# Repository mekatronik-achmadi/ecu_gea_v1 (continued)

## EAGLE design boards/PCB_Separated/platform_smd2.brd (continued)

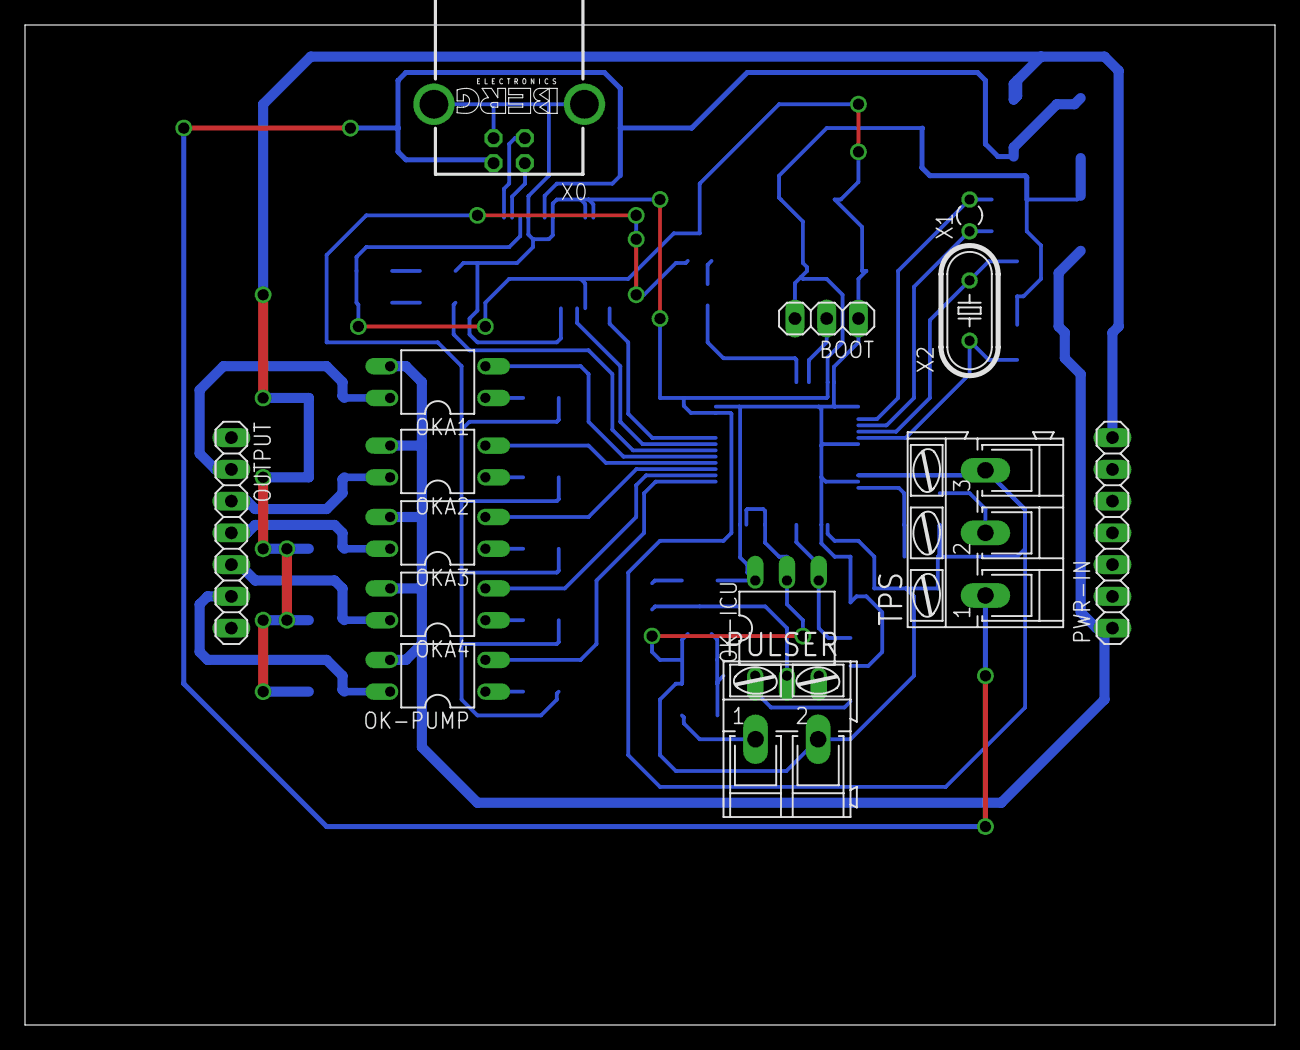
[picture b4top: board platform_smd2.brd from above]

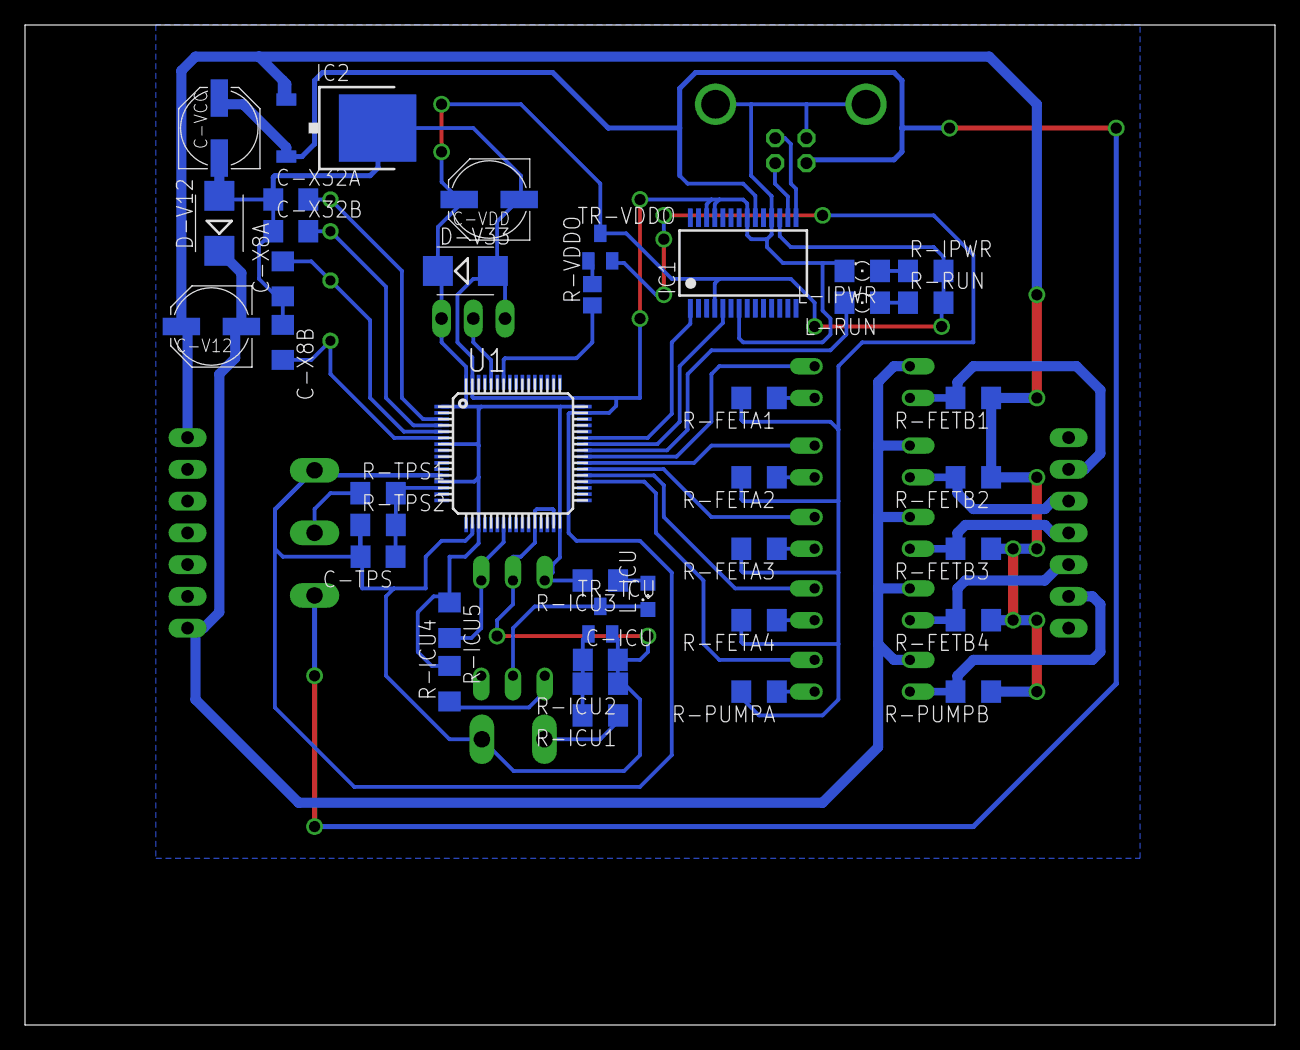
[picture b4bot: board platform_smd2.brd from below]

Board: 2 copper layers, 100.0 x 80.0 mm, 53 parts (39 on the bottom side), 43 nets.

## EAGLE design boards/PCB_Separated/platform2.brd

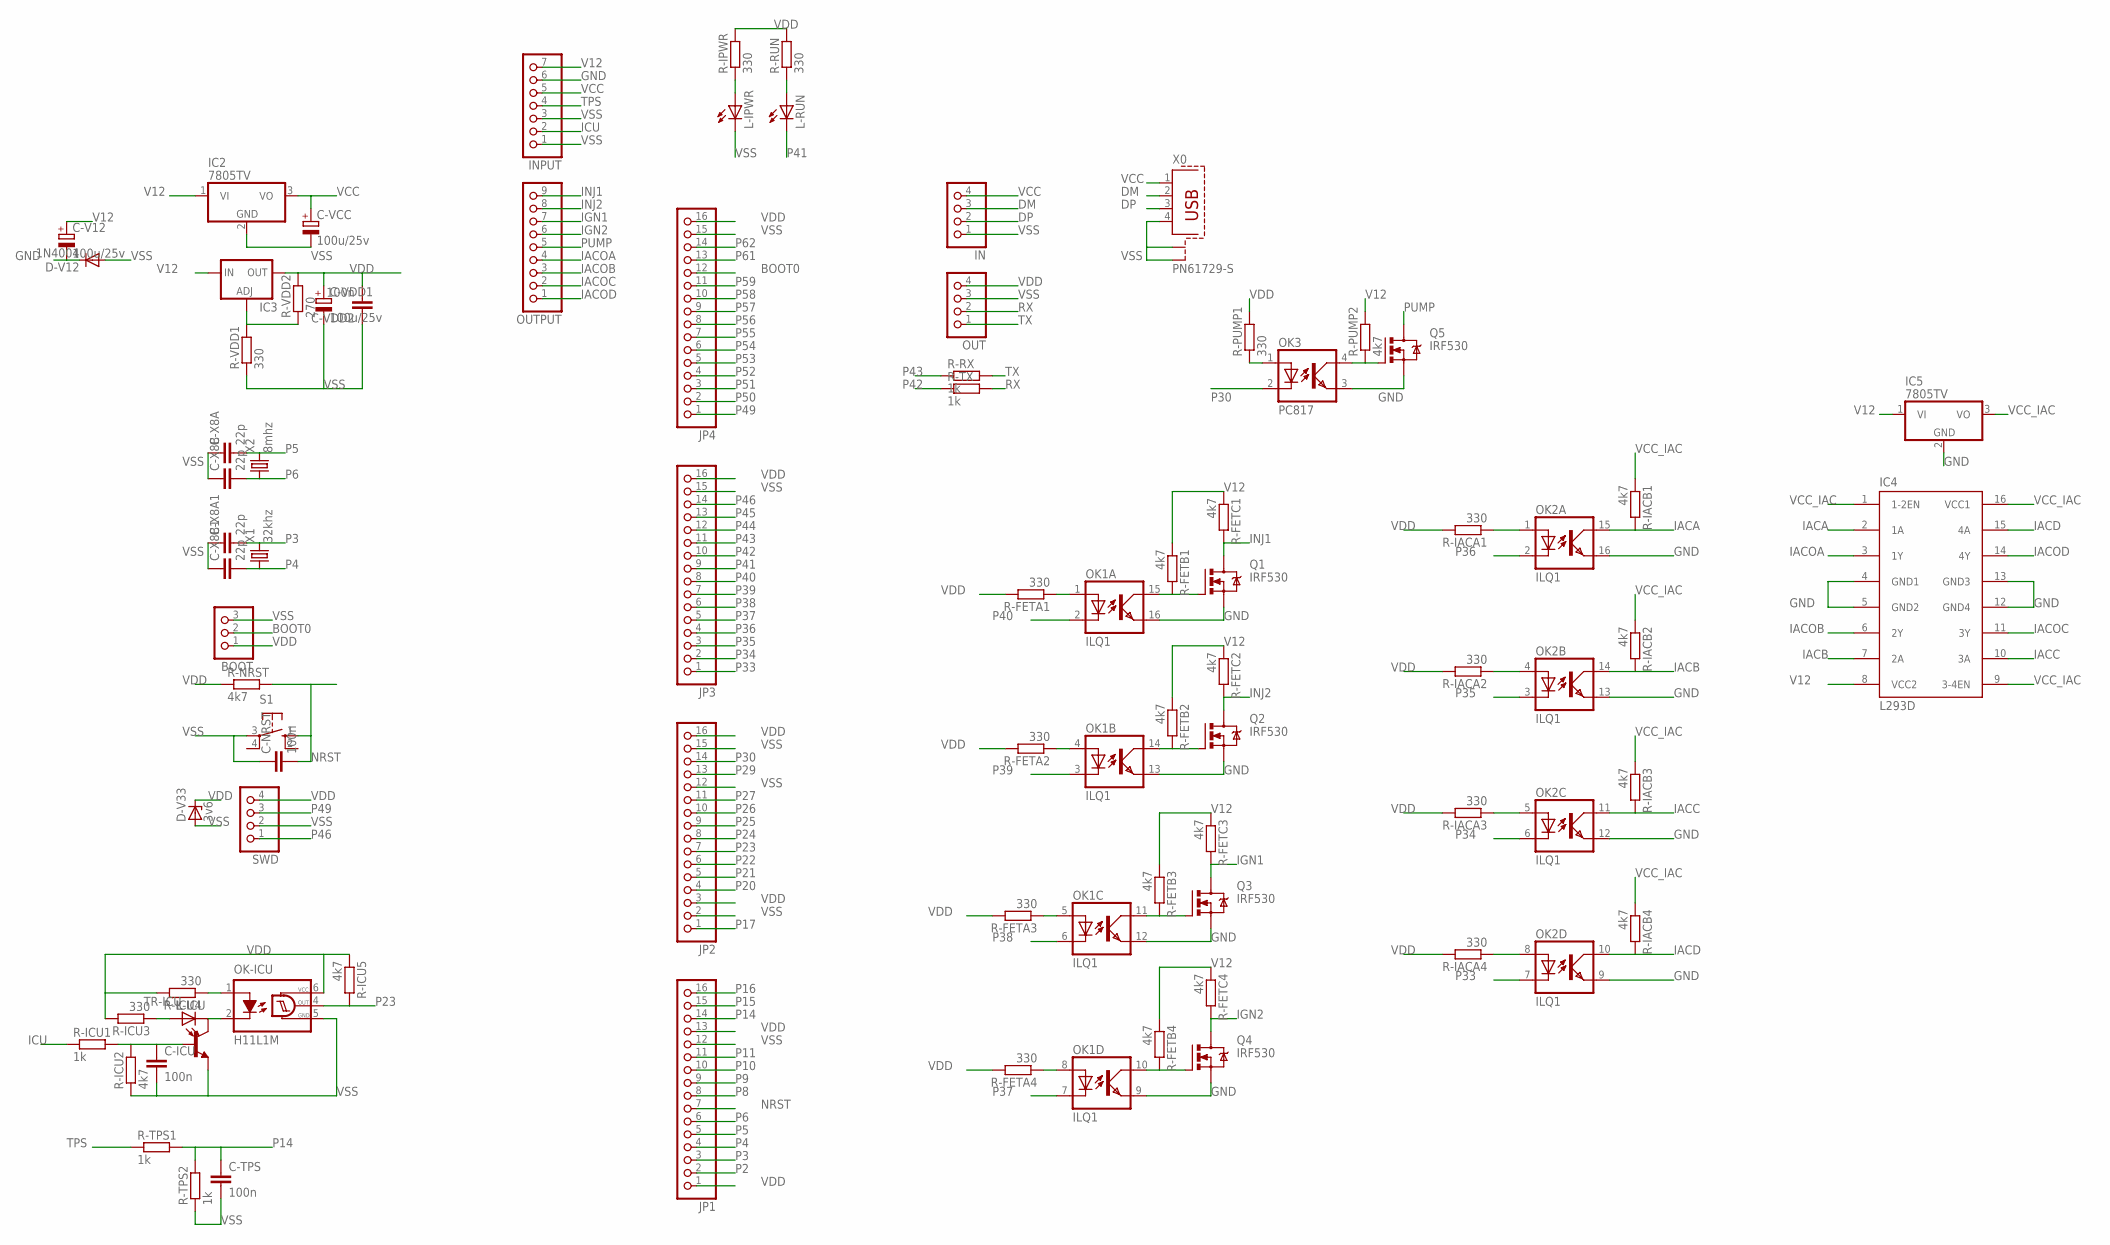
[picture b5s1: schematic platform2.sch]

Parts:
BOOT: PINHD-1X3; 1X03
C-ICU: 100n; C050-024X044
C-NRST: 100n; C050-024X044
C-TPS: 100n; C050-024X044
C-V12: 100u/25v; E2-5
C-VCC: 100u/25v; E2-5
C-VDD1: 100u/25v; E2-5
C-VDD2: 100n; C050-024X044
C-X8A, C-X8A1, C-X8B, C-X8B1: 22p; C025-024X044
D-V12: 1N4004; DO41-10
D-V33: 3v6; ZDIO-7.5
IC2, IC5: 7805TV; TO220V
IC3: LM317TS; 317TS
IC4: L293D; DIL16
IN: PINHD-1X4; 1X04
INPUT: PINHD-1X7; 1X07
JP1, JP2, JP3, JP4: PINHD-1X16; 1X16
L-ICU: LED3MM
L-IPWR: LED3MM
L-RUN: LED3MM
OK1, OK2: ILQ1; DIL16
OK3: PC817; DIL04
OK-ICU: H11L1M; DIL06
OUT: PINHD-1X4; 1X04
OUTPUT: PINHD-1X9; 1X09
Q1, Q2, Q3, Q4, Q5: IRF530; TO220BV
R-FETA1, R-FETA2, R-FETA3, R-FETA4: 330; 0204/7
R-FETB1, R-FETB2, R-FETB3, R-FETB4: 4k7; 0204/7
R-FETC1, R-FETC2, R-FETC3, R-FETC4: 4k7; 0204/7
R-IACA1, R-IACA2, R-IACA3, R-IACA4: 330; 0204/7
R-IACB1, R-IACB2, R-IACB3, R-IACB4: 4k7; 0204/7
R-ICU1: 1k; 0204/7
R-ICU2, R-ICU5: 4k7; 0204/7
R-ICU3, R-ICU4: 330; 0204/7
R-IPWR: 330; 0204/7
R-NRST: 4k7; 0204/7
R-PUMP1: 330; 0204/7
R-PUMP2: 4k7; 0204/7
R-RUN: 330; 0204/7
R-RX: 1k; 0204/7
R-TPS1, R-TPS2: 1k; 0204/7
R-TX: 1k; 0204/7
R-VDD1: 330; 0204/7
R-VDD2: 270; 0204/7
S1: 10-XX; B3F-10XX
SWD: PINHD-1X4; 1X04
TR-ICU: 2N3904-NPN-TO92-EBC; TO92-EBC
X0: PN61729-S
X1: 32khz; TC26V
X2: 8mhz; HC49U-V

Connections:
BOOT0: BOOT.2, JP4.12
DM: IN.3, X0.2
DP: IN.2, X0.3
GND: C-V12.-, D-V12.C, IC4.4 (GND1), IC4.5 (GND2), IC4.12 (GND4), IC4.13 (GND3), IC5.2 (GND), INPUT.6, OK1.9 (EMIT), OK1.12 (EMIT), OK1.13 (EMIT), OK1.16 (EMIT), OK2.9 (EMIT), OK2.12 (EMIT), OK2.13 (EMIT), OK2.16 (EMIT), OK3.3 (EMIT), Q1.S, Q2.S, Q3.S, Q4.S, Q5.S
IACA: IC4.2 (1A), OK2.15 (COL), R-IACB1.2
IACB: IC4.7 (2A), OK2.14 (COL), R-IACB2.2
IACC: IC4.10 (3A), OK2.11 (COL), R-IACB3.2
IACD: IC4.15 (4A), OK2.10 (COL), R-IACB4.2
IACOA: IC4.3 (1Y), OUTPUT.4
IACOB: IC4.6 (2Y), OUTPUT.3
IACOC: IC4.11 (3Y), OUTPUT.2
IACOD: IC4.14 (4Y), OUTPUT.1
ICU: INPUT.2, R-ICU1.1
IGN1: OUTPUT.7, Q3.D, R-FETC3.2
IGN2: OUTPUT.6, Q4.D, R-FETC4.2
INJ1: OUTPUT.9, Q1.D, R-FETC1.2
INJ2: OUTPUT.8, Q2.D, R-FETC2.2
unnamed: OK1.14 (COL), Q2.G, R-FETB2.2
unnamed: C-ICU.1, R-ICU1.2, R-ICU2.2, TR-ICU.B
unnamed: L-ICU.K (C), OK-ICU.2 (C), TR-ICU.C
unnamed: OK-ICU.1 (A), R-ICU4.1
unnamed: L-ICU.A, R-ICU3.1
unnamed: L-IPWR.A, R-IPWR.1
unnamed: L-RUN.A, R-RUN.1
unnamed: OK3.1 (A), R-PUMP1.1
unnamed: OK2.1 (A), R-IACA1.1
unnamed: OK1.15 (COL), Q1.G, R-FETB1.2
unnamed: OK1.4 (A), R-FETA2.1
unnamed: OK1.1 (A), R-FETA1.1
unnamed: OK1.11 (COL), Q3.G, R-FETB3.2
unnamed: OK1.5 (A), R-FETA3.1
unnamed: OK1.10 (COL), Q4.G, R-FETB4.2
unnamed: OK1.8 (A), R-FETA4.1
unnamed: OK2.4 (A), R-IACA2.1
unnamed: OK3.4 (COL), Q5.G, R-PUMP2.1
unnamed: OK2.5 (A), R-IACA3.1
unnamed: OK2.8 (A), R-IACA4.1
unnamed: IC3.1 (ADJ), R-VDD1.2, R-VDD2.1
NRST: C-NRST.2, JP1.7, R-NRST.2, S1.1 (S)
P2: JP1.2
P3: C-X8A1.2, JP1.3, X1.2
P4: C-X8B1.2, JP1.4, X1.1
P5: C-X8A.2, JP1.5, X2.2
P6: C-X8B.2, JP1.6, X2.1
P8: JP1.8
P9: JP1.9
P10: JP1.10
P11: JP1.11
P14: C-TPS.1, JP1.14, R-TPS1.2, R-TPS2.2
P15: JP1.15
P16: JP1.16
P17: JP2.1
P20: JP2.4
P21: JP2.5
P22: JP2.6
P23: JP2.7, OK-ICU.4 (OUT), R-ICU5.2
P24: JP2.8
P25: JP2.9
P26: JP2.10
P27: JP2.11
P29: JP2.13
P30: JP2.14, OK3.2 (C)
P33: JP3.1, OK2.7 (C)
P34: JP3.2, OK2.6 (C)
P35: JP3.3, OK2.3 (C)
P36: JP3.4, OK2.2 (C)
P37: JP3.5, OK1.7 (C)
P38: JP3.6, OK1.6 (C)
P39: JP3.7, OK1.3 (C)
P40: JP3.8, OK1.2 (C)
P41: JP3.9, L-RUN.K (C)
P42: JP3.10, R-TX.1
P43: JP3.11, R-RX.1
P44: JP3.12
P45: JP3.13
P46: JP3.14, SWD.1
P49: JP4.1, SWD.3
P50: JP4.2
P51: JP4.3
P52: JP4.4
P53: JP4.5
P54: JP4.6
P55: JP4.7
P56: JP4.8
P57: JP4.9
P58: JP4.10
P59: JP4.11
P61: JP4.13
P62: JP4.14
PUMP: OUTPUT.5, Q5.D
RX: OUT.2, R-TX.2
TPS: INPUT.4, R-TPS1.1
TX: OUT.1, R-RX.2
V12: C-V12.+, IC2.1 (VI), IC3.3 (IN), IC4.8 (VCC2), IC5.1 (VI), INPUT.7, R-FETB1.1, R-FETB2.1, R-FETB3.1, R-FETB4.1, R-FETC1.1, R-FETC2.1, R-FETC3.1, R-FETC4.1, R-PUMP2.2
VCC: C-VCC.+, IC2.3 (VO), IN.4, INPUT.5, X0.1
VCC_IAC: IC4.1 (1-2EN), IC4.9 (3-4EN), IC4.16 (VCC1), IC5.3 (VO), R-IACB1.1, R-IACB2.1, R-IACB3.1, R-IACB4.1
VDD: BOOT.1, C-VDD1.+, C-VDD2.2, D-V33.C, IC3.2 (OUT), JP1.1, JP1.13, JP2.3, JP2.16, JP3.16, JP4.16, OK-ICU.6 (VCC), OUT.4, R-FETA1.2, R-FETA2.2, R-FETA3.2, R-FETA4.2, R-IACA1.2, R-IACA2.2, R-IACA3.2, R-IACA4.2, R-ICU3.2, R-ICU4.2, R-ICU5.1, R-IPWR.2, R-NRST.1, R-PUMP1.2, R-RUN.2, R-VDD2.2, SWD.4
VSS: BOOT.3, C-ICU.2, C-NRST.1, C-TPS.2, C-VCC.-, C-VDD1.-, C-VDD2.1, C-X8A.1, C-X8A1.1, C-X8B.1, C-X8B1.1, D-V12.A, D-V33.A, IC2.2 (GND), IN.1, INPUT.1, INPUT.3, JP1.12, JP2.2, JP2.12, JP2.15, JP3.15, JP4.15, L-IPWR.K (C), OK-ICU.5 (GND), OUT.3, R-ICU2.1, R-TPS2.1, R-VDD1.1, S1.3, SWD.2, TR-ICU.E, X0.4, X0.S1, X0.S2

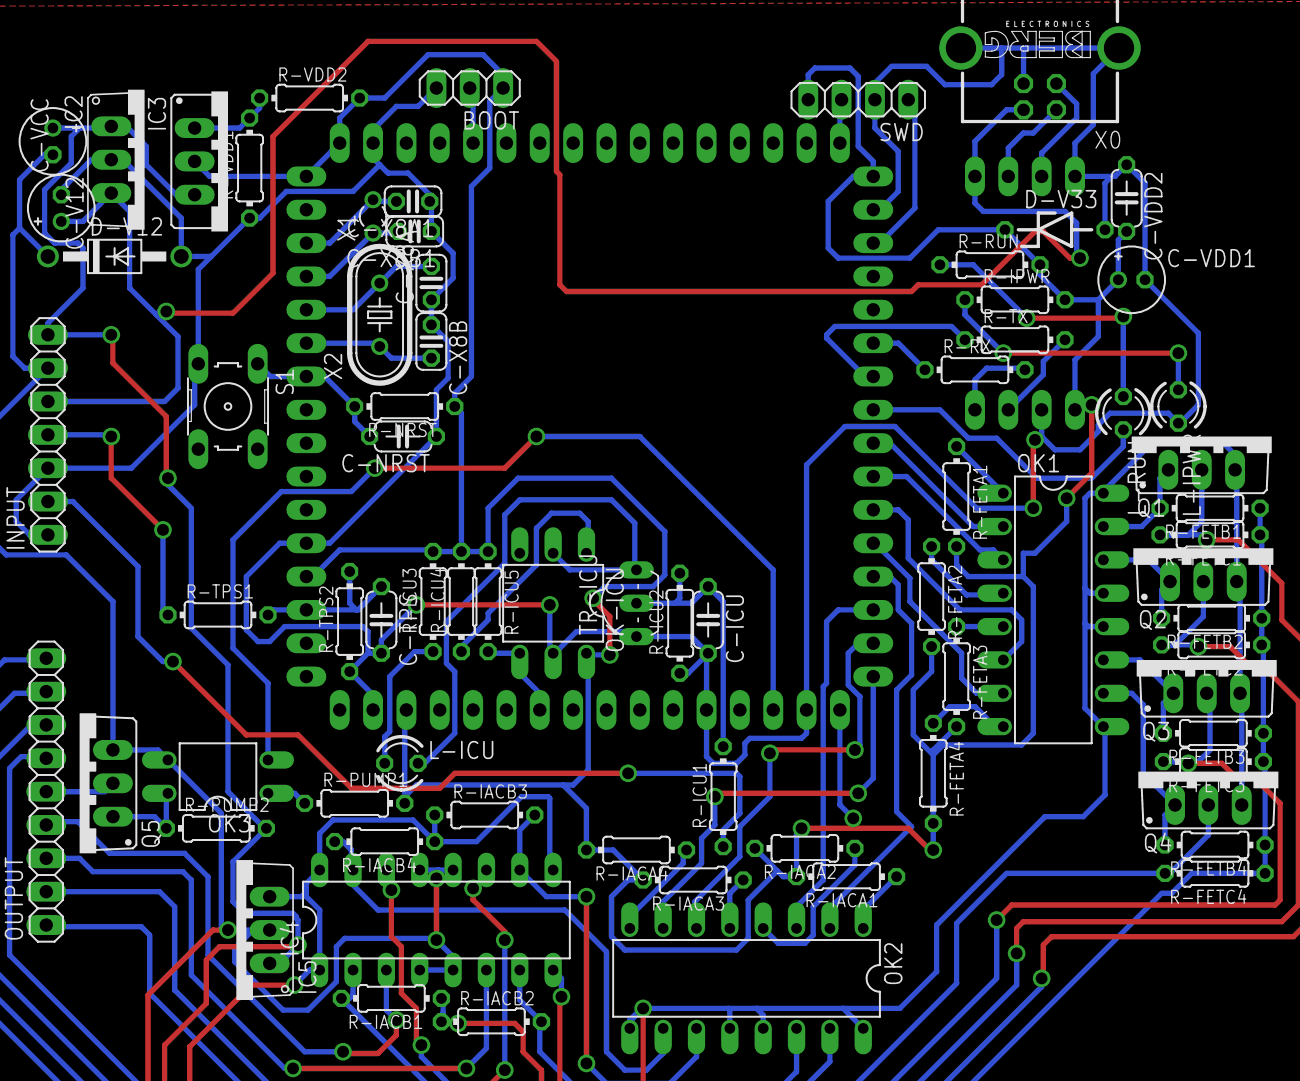
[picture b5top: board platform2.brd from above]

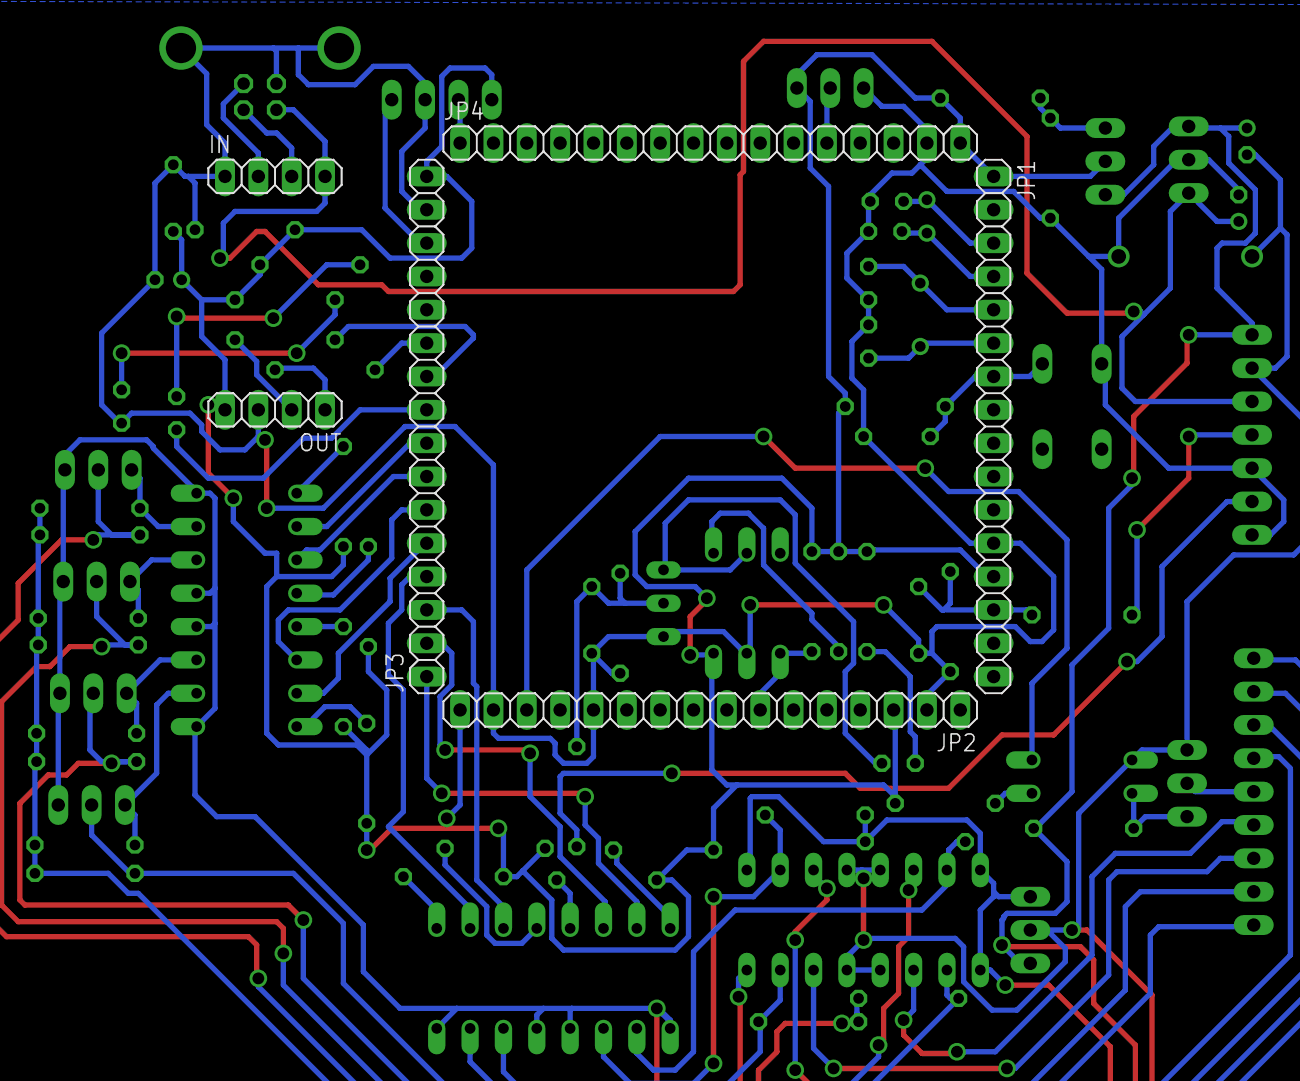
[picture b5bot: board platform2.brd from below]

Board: 2 copper layers, 80 parts (6 on the bottom side), 68 nets.

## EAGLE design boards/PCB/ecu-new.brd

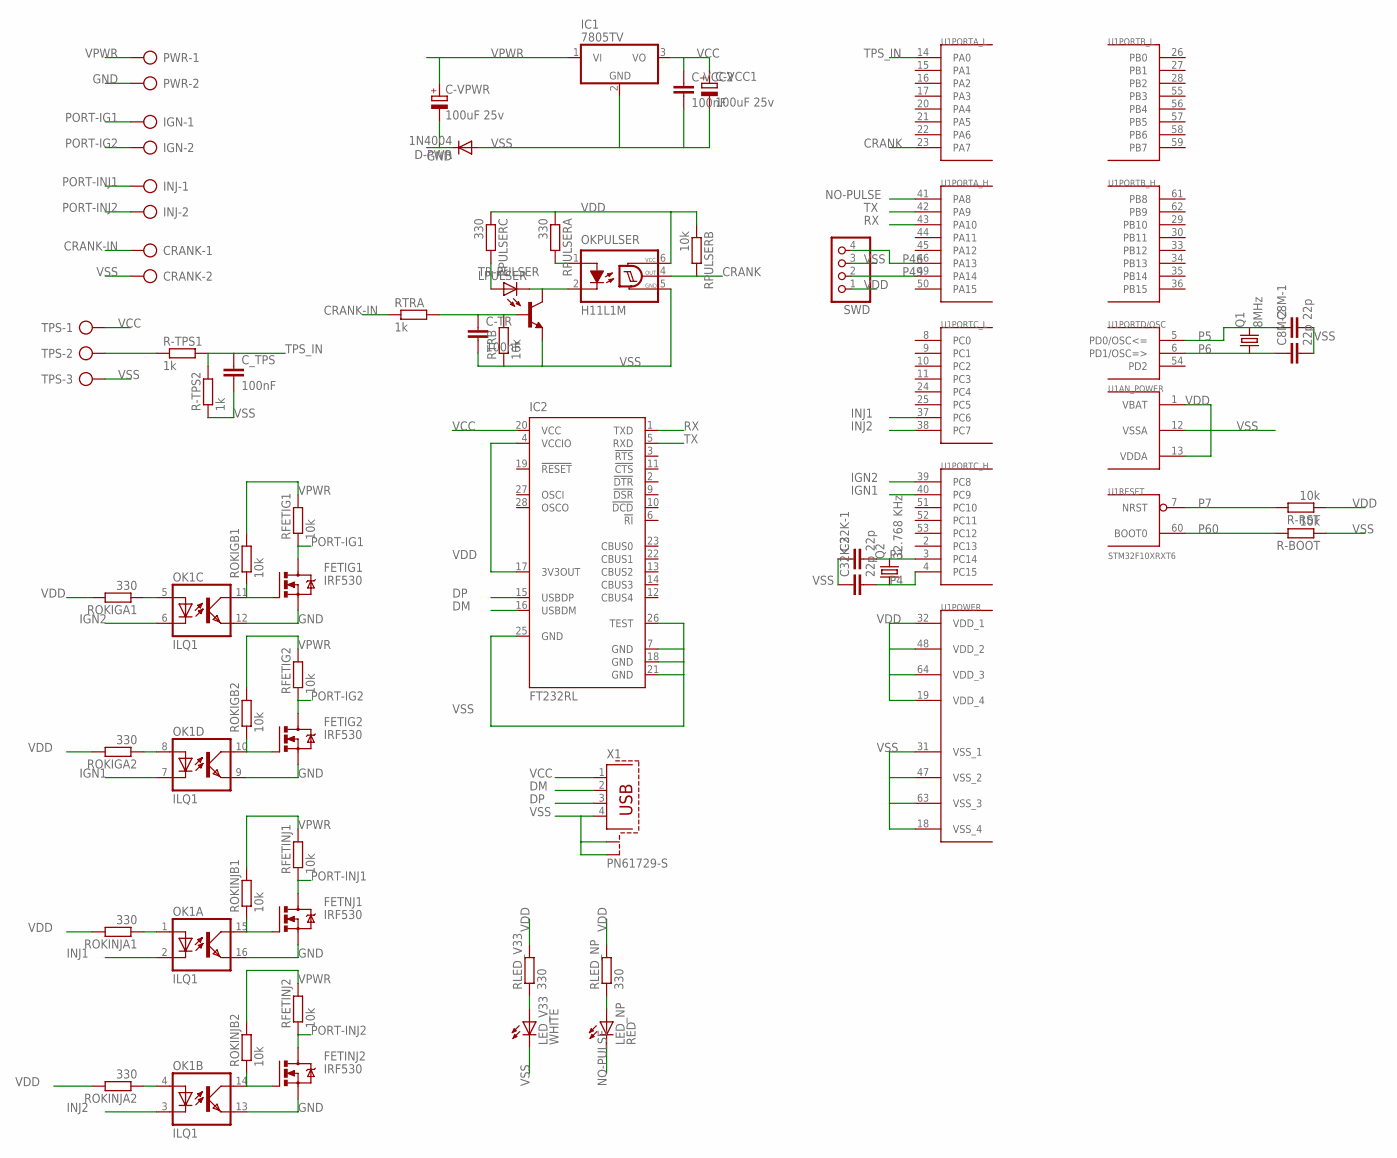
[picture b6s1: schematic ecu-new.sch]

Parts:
C8M-1, C8M-2, C32K-1, C32K-2: 22p; C025-030X050
C-TR: 100nF; C050-024X044
C-VCC1: 100uF 25v; E2,5-7
C-VCC2: 100nF; C050-024X044
C-VPWR: 100uF 25v; E2,5-7
CRANK: AK300/2
C_TPS: 100nF; C050-024X044
D-PWR: 1N4004; DO41-10
FETIG1, FETIG2: IRF530; TO220BV
FETINJ2: IRF530; TO220BV
FETNJ1: IRF530; TO220BV
IC1: 7805TV; TO220V
IC2: FT232RL; SSOP28
IGN: AK300/2
INJ: AK300/2
LED_NP: RED; LED3MM
LED_V33: WHITE; LED3MM
LPULSER: LED3MM
OK1: ILQ1; DIL16
OKPULSER: H11L1M; DIL06
PWR: AK300/2
Q1: 8MHz; HC49/S
Q2: 32.768 KHz; TC26H
R-BOOT: 10k; 0204/7
R-RST: 10k; 0204/7
R-TPS1, R-TPS2: 1k; 0204/7
RFETIG1, RFETIG2: 10k; 0204/7
RFETINJ1, RFETINJ2: 10k; 0204/7
RLED_NP: 330; 0204/7
RLED_V33: 330; 0204/7
ROKIGA1, ROKIGA2: 330; 0204/7
ROKIGB1, ROKIGB2: 10k; 0204/7
ROKINJA1, ROKINJA2: 330; 0204/7
ROKINJB1, ROKINJB2: 10k; 0204/7
RPULSERA: 330; 0204/7
RPULSERB: 10k; 0204/7
RPULSERC: 330; 0204/7
RTRA: 1k; 0204/7
RTRB: 10k; 0204/7
SWD: PINHD-1X4; 1X04
TPS: AK300/3
TR-PULSER: 2N3904-NPN-TO92-EBC; TO92-EBC
U1: STM32F10XRXT6; TQFP64
X1: PN61729-S

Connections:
CRANK: OKPULSER.4 (OUT), RPULSERB.2, U1.23 (PA7)
CRANK-IN: CRANK.1, RTRA.1
DM: IC2.16 (USBDM), X1.2
DP: IC2.15 (USBDP), X1.3
GND: C-VPWR.-, D-PWR.C, FETIG1.S, FETIG2.S, FETINJ2.S, FETNJ1.S, OK1.9 (EMIT), OK1.12 (EMIT), OK1.13 (EMIT), OK1.16 (EMIT), PWR.2
IGN1: OK1.7 (C), U1.40 (PC9)
IGN2: OK1.6 (C), U1.39 (PC8)
INJ1: OK1.2 (C), U1.37 (PC6)
INJ2: OK1.3 (C), U1.38 (PC7)
unnamed: OK1.4 (A), ROKINJA2.1
unnamed: C-TR.1, RTRA.2, RTRB.2, TR-PULSER.B
unnamed: OKPULSER.1 (A), RPULSERA.2
unnamed: LPULSER.A, RPULSERC.2
unnamed: LPULSER.K (C), OKPULSER.2 (C), TR-PULSER.C
unnamed: OK1.5 (A), ROKIGA1.1
unnamed: OK1.8 (A), ROKIGA2.1
unnamed: OK1.1 (A), ROKINJA1.1
unnamed: FETIG2.G, OK1.10 (COL), ROKIGB2.1
unnamed: FETNJ1.G, OK1.15 (COL), ROKINJB1.1
unnamed: FETIG1.G, OK1.11 (COL), ROKIGB1.1
unnamed: FETINJ2.G, OK1.14 (COL), ROKINJB2.1
unnamed: R-TPS1.1, TPS.2
unnamed: LED_V33.A, RLED_V33.1
unnamed: LED_NP.A, RLED_NP.1
NO-PULSE: LED_NP.K (C), U1.41 (PA8)
P3: C32K-1.2, Q2.2, U1.3 (PC14)
P4: C32K-2.2, Q2.1, U1.4 (PC15)
P5: C8M-1.1, Q1.2, U1.5 (PD0/OSC<=)
P6: C8M-2.1, Q1.1, U1.6 (PD1/OSC=>)
P7: R-RST.2, U1.7 (NRST)
P46: SWD.4, U1.46 (PA13)
P49: SWD.2, U1.49 (PA14)
P60: R-BOOT.2, U1.60 (BOOT0)
PORT-IG1: FETIG1.D, IGN.1, RFETIG1.1
PORT-IG2: FETIG2.D, IGN.2, RFETIG2.1
PORT-INJ1: FETNJ1.D, INJ.1, RFETINJ1.1
PORT-INJ2: FETINJ2.D, INJ.2, RFETINJ2.1
RX: IC2.1 (TXD), U1.43 (PA10)
TPS_IN: C_TPS.1, R-TPS1.2, R-TPS2.2, U1.14 (PA0)
TX: IC2.5 (RXD), U1.42 (PA9)
VCC: C-VCC1.+, C-VCC2.1, IC1.3 (VO), IC2.20 (VCC), TPS.1, X1.1
VDD: IC2.4 (VCCIO), IC2.17 (3V3OUT), OKPULSER.6 (VCC), R-RST.1, RLED_NP.2, RLED_V33.2, ROKIGA1.2, ROKIGA2.2, ROKINJA1.2, ROKINJA2.2, RPULSERA.1, RPULSERB.1, RPULSERC.1, SWD.1, U1.1 (VBAT), U1.13 (VDDA), U1.19 (VDD_4), U1.32 (VDD_1), U1.48 (VDD_2), U1.64 (VDD_3)
VPWR: C-VPWR.+, IC1.1 (VI), PWR.1, RFETIG1.2, RFETIG2.2, RFETINJ1.2, RFETINJ2.2, ROKIGB1.2, ROKIGB2.2, ROKINJB1.2, ROKINJB2.2
VSS: C8M-1.2, C8M-2.2, C32K-1.1, C32K-2.1, C-TR.2, C-VCC1.-, C-VCC2.2, CRANK.2, C_TPS.2, D-PWR.A, IC1.2 (GND), IC2.7 (GND), IC2.18 (GND), IC2.21 (GND), IC2.25 (GND), IC2.26 (TEST), LED_V33.K (C), OKPULSER.5 (GND), R-BOOT.1, R-TPS2.1, RTRB.1, SWD.3, TPS.3, TR-PULSER.E, U1.12 (VSSA), U1.18 (VSS_4), U1.31 (VSS_1), U1.47 (VSS_2), U1.63 (VSS_3), X1.4, X1.S1, X1.S2

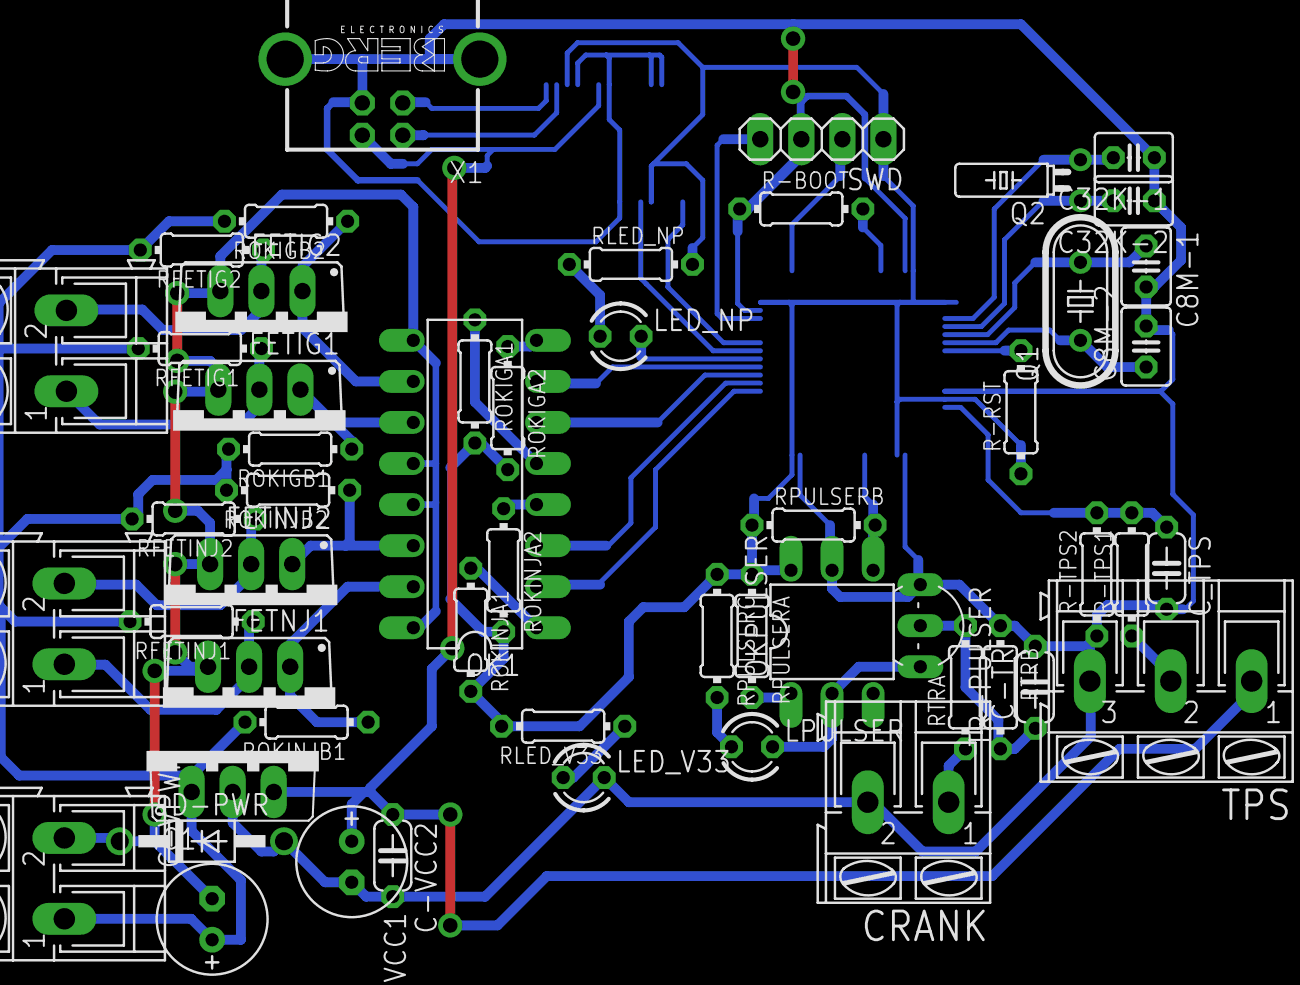
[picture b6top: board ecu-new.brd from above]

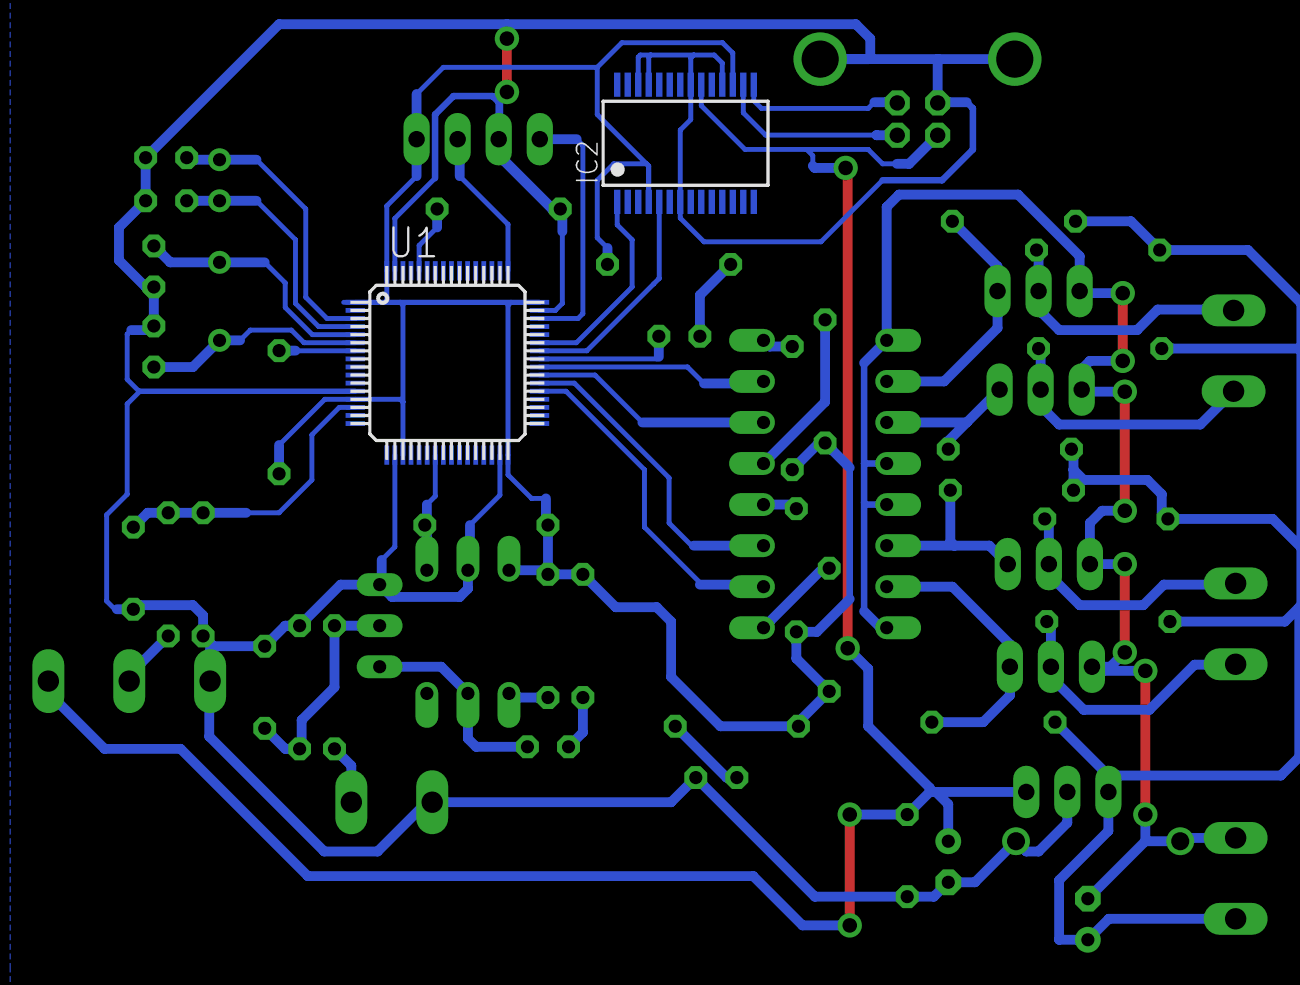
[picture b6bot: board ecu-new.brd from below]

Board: 2 copper layers, 55 parts (2 on the bottom side), 44 nets.

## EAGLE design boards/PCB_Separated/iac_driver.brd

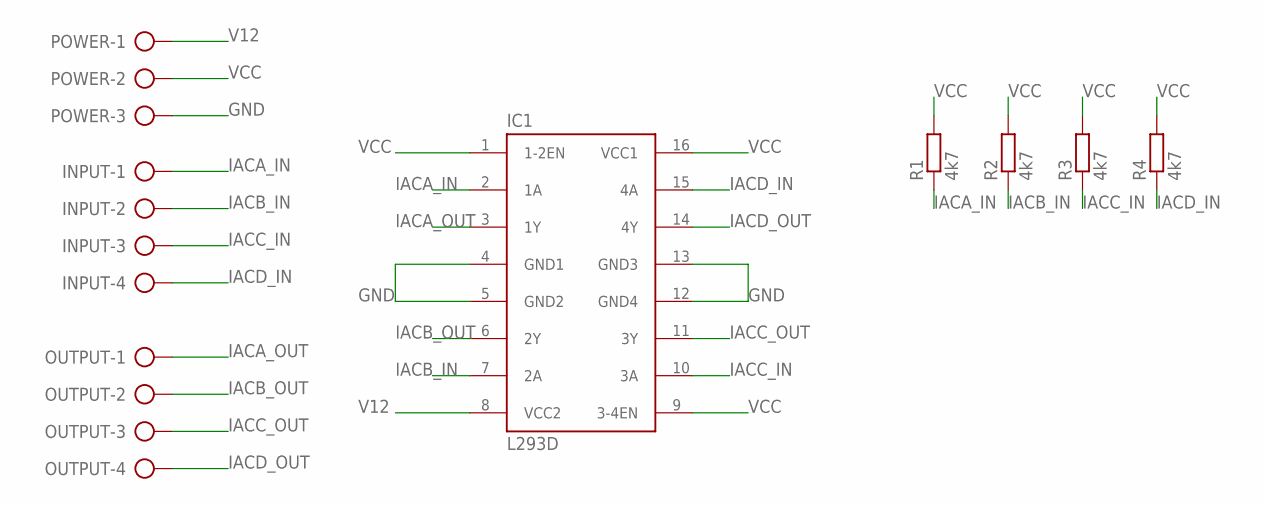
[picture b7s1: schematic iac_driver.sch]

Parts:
IC1: L293D; DIL16
INPUT: AK500/4
OUTPUT: AK500/4
POWER: AK500/3
R1, R2, R3, R4: 4k7; 0204/7

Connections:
GND: IC1.4 (GND1), IC1.5 (GND2), IC1.12 (GND4), IC1.13 (GND3), POWER.3
IACA_IN: IC1.2 (1A), INPUT.1, R1.1
IACA_OUT: IC1.3 (1Y), OUTPUT.1
IACB_IN: IC1.7 (2A), INPUT.2, R2.1
IACB_OUT: IC1.6 (2Y), OUTPUT.2
IACC_IN: IC1.10 (3A), INPUT.3, R3.1
IACC_OUT: IC1.11 (3Y), OUTPUT.3
IACD_IN: IC1.15 (4A), INPUT.4, R4.1
IACD_OUT: IC1.14 (4Y), OUTPUT.4
V12: IC1.8 (VCC2), POWER.1
VCC: IC1.1 (1-2EN), IC1.9 (3-4EN), IC1.16 (VCC1), POWER.2, R1.2, R2.2, R3.2, R4.2

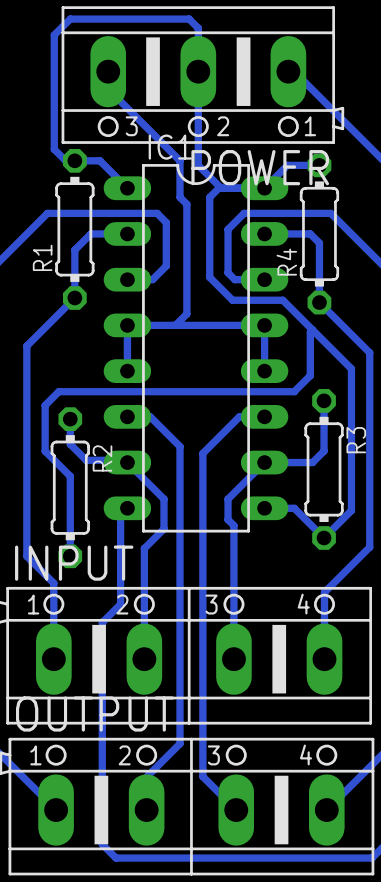
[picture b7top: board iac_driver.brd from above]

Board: 2 copper layers, 8 parts (0 on the bottom side), 11 nets.

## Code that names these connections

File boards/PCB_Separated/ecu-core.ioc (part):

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Mcu.Name=STM32F103R(8-B)Tx
Mcu.Package=LQFP64
PA0-WKUP.Mode=IN0
PA0-WKUP.Signal=ADC1_IN0
PA1.Mode=IN1
PA1.Signal=ADC1_IN1
PA10.Mode=Asynchronous
PA10.Signal=USART1_RX
PA13.Mode=Serial-Wire
PA13.Signal=SYS_JTMS-SWDIO
PA14.Mode=Serial-Wire
PA14.Signal=SYS_JTCK-SWCLK
PA2.Mode=IN2
PA2.Signal=ADC1_IN2
PA3.Mode=IN3
PA3.Signal=ADC1_IN3
PA7.Mode=PWM-Input-2
PA7.Signal=TIM3_CH2
PA8.Signal=GPIO_Output
PA9.Mode=Asynchronous
PA9.Signal=USART1_TX
PB12.Signal=GPIO_Output
PB13.Signal=GPIO_Output
PB14.Signal=GPIO_Output
PB15.Signal=GPIO_Output
PB6.Signal=GPIO_Output
PB7.Signal=GPIO_Output
PC14-OSC32_IN.Mode=LSE-External-Oscillator
PC14-OSC32_IN.Signal=SYS_OSC32_IN
PC15-OSC32_OUT.Mode=LSE-External-Oscillator
PC15-OSC32_OUT.Signal=SYS_OSC32_OUT
PC6.Signal=GPIO_Output
PC7.Signal=GPIO_Output
PC8.Signal=GPIO_Output
PC9.Signal=GPIO_Output
PD0-OSC_IN.Mode=HSE-External-Oscillator
PD0-OSC_IN.Signal=SYS_OSC_IN
PD1-OSC_OUT.Mode=HSE-External-Oscillator
PD1-OSC_OUT.Signal=SYS_OSC_OUT

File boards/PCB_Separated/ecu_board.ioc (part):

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Mcu.Name=STM32F103R(8-B)Tx
Mcu.Package=LQFP64
PA0-WKUP.Mode=IN0
PA0-WKUP.Signal=ADC1_IN0
PA1.Mode=IN1
PA1.Signal=ADC1_IN1
PA10.Mode=Asynchronous
PA10.Signal=USART1_RX
PA2.Mode=IN2
PA2.Signal=ADC1_IN2
PA3.Mode=IN3
PA3.Signal=ADC1_IN3
PA4.Mode=IN4
PA4.Signal=ADC1_IN4
PA5.Mode=IN5
PA5.Signal=ADC1_IN5
PA7.Mode=PWM-Input-2
PA7.Signal=TIM3_CH2
PA9.Mode=Asynchronous
PA9.Signal=USART1_TX
PB12.Signal=GPIO_Output
PB13.Signal=GPIO_Output
PB14.Signal=GPIO_Output
PB15.Signal=GPIO_Output
PB2.Signal=GPIO_Input
PC14-OSC32_IN.Mode=LSE-External-Oscillator
PC14-OSC32_IN.Signal=SYS_OSC32_IN
PC15-OSC32_OUT.Mode=LSE-External-Oscillator
PC15-OSC32_OUT.Signal=SYS_OSC32_OUT
PC6.Signal=GPIO_Output
PC7.Signal=GPIO_Output
PC8.Signal=GPIO_Output
PC9.Signal=GPIO_Output
PD0-OSC_IN.Mode=HSE-External-Oscillator
PD0-OSC_IN.Signal=SYS_OSC_IN
PD1-OSC_OUT.Mode=HSE-External-Oscillator
PD1-OSC_OUT.Signal=SYS_OSC_OUT

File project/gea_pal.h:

#ifndef GEA2_PAL
#define GEA2_PAL

#define led 8

#define inj_1 9
#define inj_2 8
#define ign_1 7
#define ign_2 6
#define pump 15

//sistem tanpa pullup
//#define output 6
//sistem dengan pullup
#define output 14

#define no_pulse palTogglePad(GPIOA,led)

#define on_inj1 palSetPad(GPIOC,inj_1)
#define off_inj1 palClearPad(GPIOC,inj_1)

#define on_inj2 palSetPad(GPIOC,inj_2)
#define off_inj2 palClearPad(GPIOC,inj_2)

#define off_ign1 palSetPad(GPIOC,ign_1)
#define on_ign1 palClearPad(GPIOC,ign_1)

#define off_ign2 palSetPad(GPIOC,ign_2)
#define on_ign2 palClearPad(GPIOC,ign_2)

#define on_pump palSetPad(GPIOB,pump)
#define off_pump palClearPad(GPIOB,pump)

//sistem tanpa pullup
//#define out_active palSetPad(GPIOB,output)
//sistem dengan pullup
#define out_active palSetPad(GPIOB,output)

#define interval chThdSleepMilliseconds(6);

#define IACA 15
#define IACB 14
#define IACC 13
#define IACD 12

#define IACA_H palSetPad(GPIOB,IACA)
#define IACA_L palClearPad(GPIOB,IACA)

#define IACB_H palSetPad(GPIOB,IACB)
#define IACB_L palClearPad(GPIOB,IACB)

#define IACC_H palSetPad(GPIOB,IACC)
#define IACC_L palClearPad(GPIOB,IACC)

#define IACD_H palSetPad(GPIOB,IACD)
#define IACD_L palClearPad(GPIOB,IACD)

void Pal_Setup(void);
void Iac_CW(uint8_t loop);
void Iac_CCW(uint8_t loop);
void Iac_Start(void);

#endif  

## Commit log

2014-03-09 add a new separatedly-style board
2014-03-10 Change License to GPL v3
2014-03-10 Modify Board. Core and FTDI become one file
2014-03-11 add platform board
2014-03-15 Proceed to use GPT
2014-03-15 added GPT functions
2014-03-15 1st GPT use trial
2014-03-15 edit serial interface data
2014-03-16 perbaikan konversi sudut ke tick timer
2014-03-18 Improve engine settings and add shell data_and_test routine
2014-03-18 improved test and data function
2014-03-19 re-add info function to shell
2014-03-20 add some toggle action to output
2014-03-22 copy from james's PC
2014-03-26 -delete a useless sch pics -add ecu io pins diagram -add a GND to VSS line on FTDI. Hopefully internally connected with other GND pins -progress new separated ecu board.
2014-03-26 progress to build new ecu boards
2014-03-26 progress add function to IAC
2014-04-04 add connector board
2014-04-04 add label on connector design
2014-04-08 re-config output to Injector and Ignitor
2014-04-09 progress buat IAC
2014-04-10 progress for IAC
    move resistor on mainborad to IAC driver to get 5v logic instead of 12v logic
2014-04-13 IAC progress. Valve already driven, but there a problem with voltage while USB connected to PC
2014-04-13 add more cycle for opening iac (CCW rotation)
    L293D circuit should use separate VCC regulator
2014-04-13 IAC over opened
2014-04-13 IAC still bad performance
2014-04-16 new commit and IAC progress
2014-04-17 IAC seem good
2014-04-22 add Qt-based Engine Interface and Qt-based Engine Calculator
2014-04-23 interface progress
2014-04-26 progress interface
2014-05-02 eeprom emulation
2014-05-03 -memory and interfacing on embedded core seems good by increase max argument on shell -GUI on Qt still on progress
2014-05-04 Interface rancangan oke
2014-05-04 - move injection trigger to TDC
    -next:
    1. injection duration to 2D Array (RPM and TPS)
    2. injection off to RPM settings
2014-05-04 still bad
2014-05-11 problem with tick for 1 degree
2014-05-12 progress semakin pusing
2014-05-12 Idle seems good
    next:
    1. try accel and de-accel
2014-05-17 board integrated & double-layered
2014-05-19 gak jadi bikin pcb baru dulu
2014-05-21 add new board but same schematic
    next:
    - fix startup firing bug
    - add enrichment sensor
    - interface for setting
2014-05-29 working on interface
2014-06-12 interface to do:
    add save and load
2014-06-13 add open_ms time and base_ms time add iac control to interface
2014-06-15 run test
2014-06-16 run test again
2014-06-22 tinggal save
2014-06-23 nambah input analog untuk map, mat,clt
2014-06-24 add fitur to save and load on interface
2014-06-24 add logo ITS
2014-06-25 calculator sudah diskontinue
    interface untuk windows siap
2014-06-25 fix port name combo box
2014-06-25 Add Bill Of Material untuk platform_smd2_map dan platform_smd2_driver
    note: desain platform_smd2_map pada L-ICU masih dengan led 0805 dan harus diganti dengan led 1206
2014-06-26 perbaikan desain board
2014-06-27 fix some bugs
2014-06-30 ~nilai injeksi yang dibalik sesuai TPS ~tambahan untuk kendali periodik pompa
2014-07-03 coolant measurement
2014-07-03 coolant progress
2014-07-04 coolant value avoid from overflow
2014-07-04 int conversion miss
2014-07-05 pump setting
2014-07-10 new baord with o2 analog input
2014-07-17 all featured board versi 1
2014-08-05 add batik background
2014-08-07 add batik for interface on win32
2014-08-07 win32 serial fix
2014-09-03 revisi driver
2014-09-16 revisi board driver v2
2014-09-28 edit mini usb and deactivate delayed startup
2018-10-23 engine calculator
